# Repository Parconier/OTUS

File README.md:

# OTUS: 3D Printed Robotics Kit by Parconier 

[Click here to purchase one from the Abierto shop](https://www.abierto.cc/shop/#tags=10849|10852 "abierto.cc")

# Files in this repository

.STL - This files are for 3D printing, if you want to edit any of them, feel free to use the .STEP file.
.STEP - This files contains every pattern in a generic 3D format that you can easily edit.

# Name format

name of the piece "\_" suggestion of color of neutral "\_" ammount per kit "\- v" version of the file

Example:
Patternx2\_color\_x6 \-  v1.0

# License

Copyright CERN 2013. 

This documentation describes Open Hardware and is licensed under the CERN OHL v. 1.2. This means that you are free to use, reproduce, sell or modify our designs in any way you see fit, as long as you retain this same license for your projects using our work. For those wanting to use our hardware designs and/or software packages, we require you:

Label the product as a clone. It must be clear that it is not a product from our factory.
Note that "OTUS is a registered trademark of Parconier".
Host your own copy of the source files on your own server or similar, even if they are unmodified. Do not just point to our existing source.

You may redistribute and modify this documentation under the terms of the CERN OHL v.1.2. (http://ohwr.org/cernohl). This documentation is distributed WITHOUT ANY EXPRESS OR IMPLIED WARRANTY, INCLUDING OF MERCHANTABILITY, SATISFACTORY QUALITY AND FITNESS FOR A PARTICULAR PURPOSE. Please see the CERN OHL v.1.2 for applicable conditions.

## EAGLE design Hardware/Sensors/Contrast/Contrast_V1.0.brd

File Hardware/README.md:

# PCB files for the OTUS 3D Printed Robotics Kit  

[Click here to purchase OTUS PCB boards from the Abierto shop](https://www.abierto.cc/shop/product/67049/otus-electronica/ "abierto.cc")

 Format is EagleCAD for Schematic and board layout.

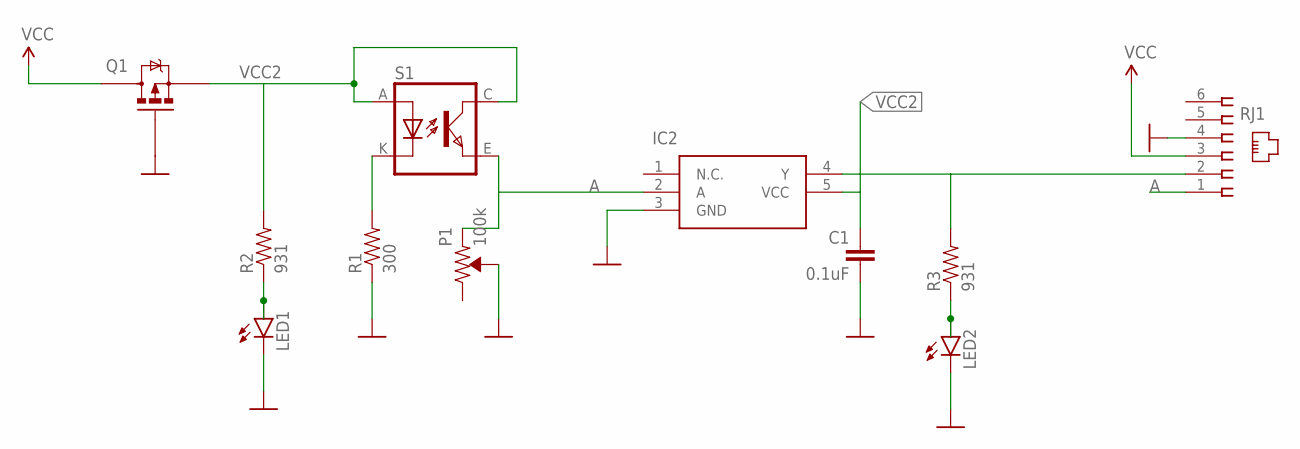
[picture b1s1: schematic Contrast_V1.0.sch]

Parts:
C1: 0.1uF; 0402; MPN CC0402KRX5R9BB104
IC2: 74LVC1G14GW-Q100,1; SOT65P212X110-5N; MPN 74AHC1G14GW-Q100,1
LED1: LED0603; LED-0603; MPN LTST-C193KRKT-5A
LED2: LED0603; LED-0603; MPN LB Q39E-L2OO-35-1
P1: 100k; 3309W-1-104; MPN 3309W-1-104
Q1: RU1C002ZPTCL; SOTFL65P210X105-3N; MPN RU1C002ZPTCL
R1: 300; RESC1005X35; MPN RC0402JR-07300RL
R2, R3: 931; RESC1005X35; MPN RC0402FR-07931RL
RJ1: 615006138421; MPN 54601-906WPLF
S1: TCRT5000; MPN TCRT5000

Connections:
A: IC2.2 (A), P1.1 (CCW), RJ1.1, S1.E (EMITTER)
GND: C1.2, IC2.3 (GND), LED1.C, LED2.C, P1.2 (WIPER), Q1.1 (G), R1.1, RJ1.4
unnamed: R1.2, S1.K (CATHODE)
unnamed: IC2.4 (Y), R3.2, RJ1.2
unnamed: LED2.A, R3.1
unnamed: LED1.A, R2.1
VCC: Q1.3 (D), RJ1.3
VCC2: C1.1, IC2.5 (VCC), Q1.2 (S), R2.2, S1.A (ANODE), S1.C (COLLECTOR)

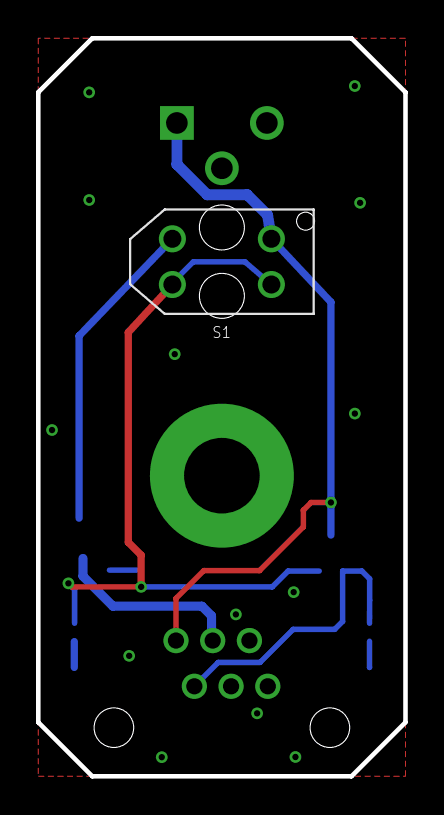
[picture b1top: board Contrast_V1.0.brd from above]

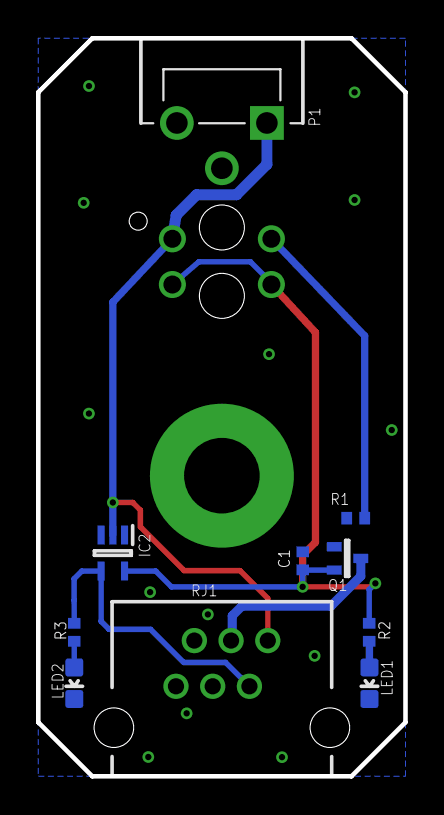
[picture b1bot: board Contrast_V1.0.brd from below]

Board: 2 copper layers, 20.4 x 41.0 mm, 11 parts (10 on the bottom side), 8 nets.

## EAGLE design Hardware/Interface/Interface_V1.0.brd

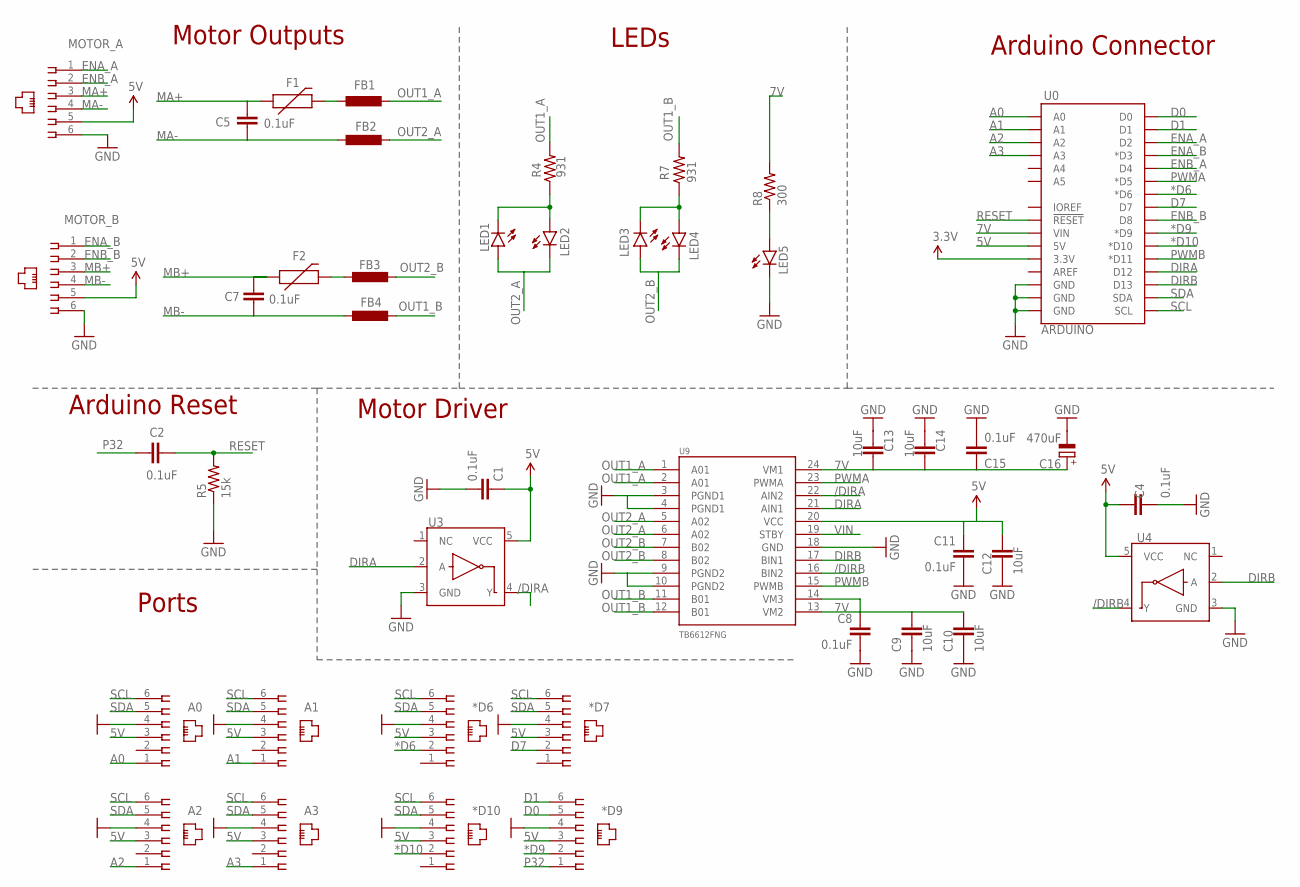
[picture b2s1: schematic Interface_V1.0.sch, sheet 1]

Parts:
*D6, *D7, *D9, *D10: 615006138421; MPNCH 623-PCB-6P6C
A0, A1, A2, A3: 615006138421; MPNCH 623-PCB-6P6C
C1, C2, C4, C5, C7, C8, C11, C15: 0.1uF; 0402; MPN CC0402KRX5R9BB104
C9, C10, C12, C13, C14: 10uF; C0603; MPN ZRB18AR61E106ME01L
C16: 470uF; PANASONIC_E; MPN EDH477M016A9MAA
F1, F2: PTC; PTC-1206; MPN 0ZCJ0100FF2E
FB1, FB2, FB3, FB4: FERRITE_BEAD; F0805; MPN 2508056017Y2
LED1, LED2, LED3, LED4: LED0603; LED-0603; MPN LTST-C193KRKT-5A
LED5: LED0603; LED-0603; MPN LW Q38G-Q2OO-3K5L-1
MOTOR_A: 615006138421; MPNCH 9901-6P6C
MOTOR_B: 615006138421; MPNCH 9901-6P6C
R4, R7: 931; RESC1005X35; MPN RC0402FR-07931RL
R5: 15k; RESC1005X35; MPN RC0402FR-0715KL
R8: 300; RESC1005X35; MPN RC0402JR-07300RL
U0: ARDUINO; ARDUINO_R3_NO_HOLES_SPI
U3, U4: INVERTER""; SC70; MPN 74AHC1G14GW-Q100,1
U9: TB6612FNG; SSOP24; MPN TB6612FNG,C,8,EL

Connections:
3.3V: U0.3.3V
5V: *D6.3, *D7.3, *D9.3, *D10.3, A0.3, A1.3, A2.3, A3.3, C1.1, C4.1, C11.1, C12.1, MOTOR_A.5, MOTOR_B.5, U0.5V, U3.5 (VCC), U4.5 (VCC), U9.20 (VCC)
7V: C8.1, C9.1, C10.1, C13.1, C14.1, C15.1, C16.+, R8.2, U0.VIN, U9.13 (VM2), U9.14 (VM3), U9.24 (VM1); also elsewhere on the board
*D6: *D6.2, U0.D6 (*D6)
*D9: *D9.2, U0.D9 (*D9)
*D10: *D10.2, U0.D10 (*D10)
/DIRA: U3.4 (Y), U9.22 (AIN2)
/DIRB: U4.4 (Y), U9.16 (BIN2)
A0: A0.1, U0.A0
A1: A1.1, U0.A1
A2: A2.1, U0.A2
A3: A3.1, U0.A3
D0: *D9.5, U0.D0
D1: *D9.6, U0.D1
D7: *D7.2, U0.D7
DIRA: U0.D12, U3.2 (A), U9.21 (AIN1)
DIRB: U0.D13, U4.2 (A), U9.17 (BIN1)
ENA_A: MOTOR_A.1, U0.D2
ENA_B: MOTOR_B.1, U0.D3 (*D3)
ENB_A: MOTOR_A.2, U0.D4
ENB_B: MOTOR_B.2, U0.D8
GND: *D6.4, *D7.4, *D9.4, *D10.4, A0.4, A1.4, A2.4, A3.4, C1.2, C4.2, C8.2, C9.2, C10.2, C11.2, C12.2, C13.2, C14.2, C15.2, C16.-, LED5.C, MOTOR_A.6, MOTOR_B.6, R5.1, U0.GND@1 (GND), U0.GND@2 (GND), U0.GND@3 (GND), U3.3 (GND), U4.3 (GND), U9.3 (PGND1), U9.4 (PGND1), U9.9 (PGND2), U9.10 (PGND2), U9.18 (GND); also elsewhere on the board
MA+: C5.1, F1.1, MOTOR_A.3
MA-: C5.2, FB2.1, MOTOR_A.4
MB+: C7.1, F2.1, MOTOR_B.3
MB-: C7.2, FB4.1, MOTOR_B.4
unnamed: LED1.C, LED2.A, R4.1
unnamed: LED3.C, LED4.A, R7.1
unnamed: F1.2, FB1.1
unnamed: F2.2, FB3.1
unnamed: LED5.A, R8.1
OUT1_A: FB1.2, R4.2, U9.1 (A01), U9.2 (A01)
OUT1_B: FB4.2, R7.2, U9.11 (B01), U9.12 (B01)
OUT2_A: FB2.2, LED1.A, LED2.C, U9.5 (A02), U9.6 (A02)
OUT2_B: FB3.2, LED3.A, LED4.C, U9.7 (B02), U9.8 (B02)
P32: *D9.1, C2.1
PWMA: U0.D5 (*D5), U9.23 (PWMA)
PWMB: U0.D11 (*D11), U9.15 (PWMB)
RESET: C2.2, R5.2, U0.RESET@1 (!RESET!)
SCL: *D6.6, *D7.6, *D10.6, A0.6, A1.6, A2.6, A3.6, U0.SCL
SDA: *D6.5, *D7.5, *D10.5, A0.5, A1.5, A2.5, A3.5, U0.SDA
VIN: U9.19 (STBY); also elsewhere on the board

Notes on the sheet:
Motor Outputs
LEDs
Arduino Connector
Motor Driver
Arduino Reset
Ports

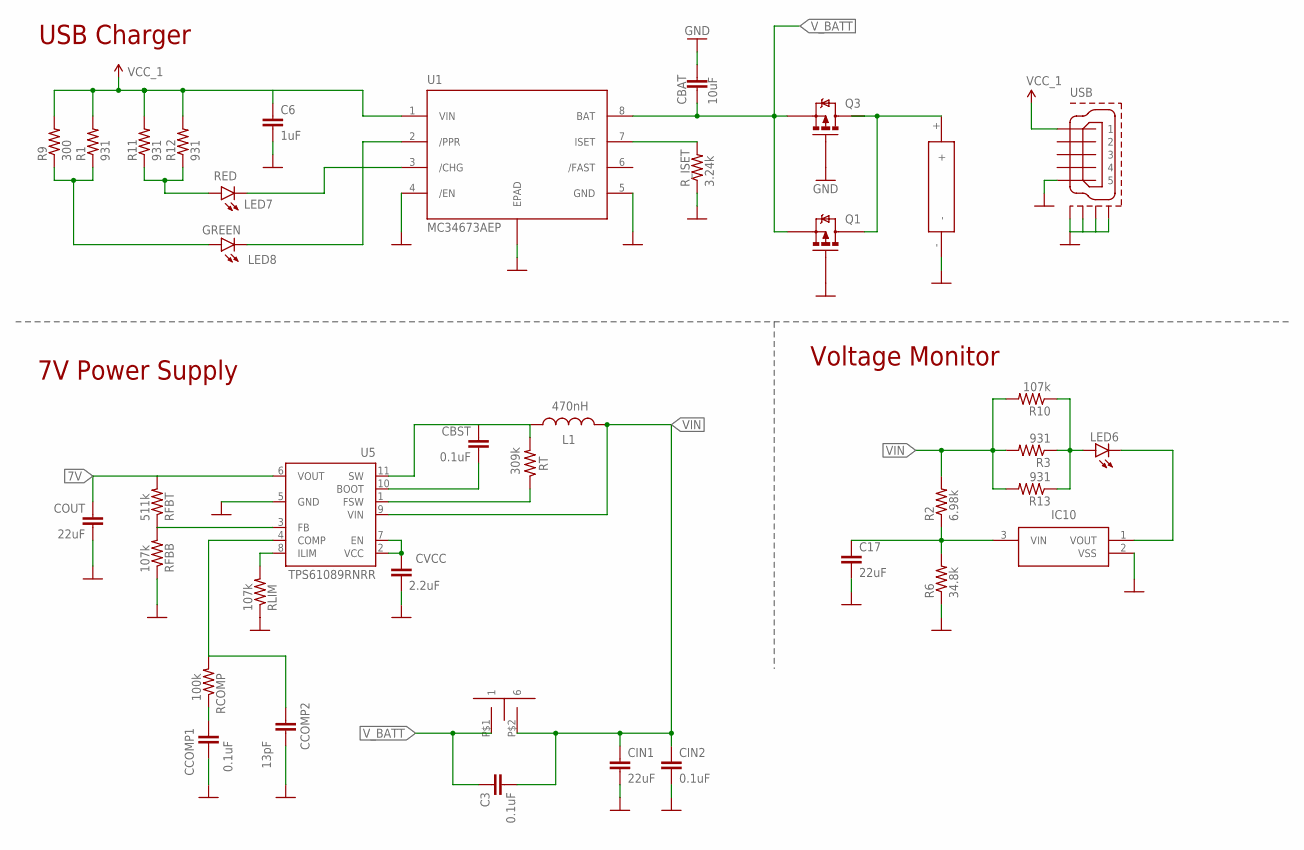
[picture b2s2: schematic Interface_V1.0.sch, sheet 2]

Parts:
B1: GPTS203212B; GPTS_RIGHT_ANGLE; MPN GPTS203212B
BATT: BATTERY; THM_HOLDER; MPN 1043
C3: 0.1uF; 0402; MPN CC0402KRX5R9BB104
C6: 1uF; 0402; MPN CC0402ZRY5V6BB105
C17: 22uF; C0603; MPN GRM188R61A226ME15D
CBAT: 10uF; C0603; MPN ZRB18AR61E106ME01L
CBST: 0.1uF; 0402; MPN CC0402KRX5R9BB104
CCOMP1: 0.1uF; 0402; MPN CC0402KRX5R9BB104
CCOMP2: 13pF; 0402; MPN CL05C130JB5NCNC
CIN1: 22uF; C0603; MPN GRM188R61A226ME15D
CIN2: 0.1uF; 0402; MPN CC0402KRX5R9BB104
COUT: 22uF; C1210; MPN GRM32ER61E226KE15L
CVCC: 2.2uF; C0603; MPN GRM188R61E225MA12D
IC10: TC54VN3002ECB713; SOT95P275X130-3N; MPN TC54VN3002ECB713
L1: 470nH; L2520; MPN DFE252012P-R47M=P2
LED6, LED7: LED0603; LED-0603; MPN LTST-C193KRKT-5A
LED8: LED0603; LED-0603; MPN LT Q39E-Q1OO-25-1
Q1: IRLML2244TRPBF; SOT95P237X112-3N; MANUFACTURER_PART_NUMBER IRLML2244TRPBF
Q3: IRLML2244TRPBF; SOT95P237X112-3N; MPN IRLML2244TRPBF
R1, R3, R11, R12, R13: 931; RESC1005X35; MPN RC0402FR-07931RL
R2: 6.98k; RESC1005X35; MPN RC0402FR-076K98L
R6: 34.8k; RESC1005X35; MPN RC0402FR-0734K8L
R9: 300; RESC1005X35; MPN RC0402JR-07300RL
R10: 107k; RESC1005X35; MPN RC0402FR-07107KL
RCOMP: 100k; RESC1005X35; MPN RC0402FR-07100KL
RFBB: 107k; RESC1005X35; MPN RC0402FR-07107KL
RFBT: 511k; RESC1005X35; MPN RC0402FR-07511KL
RLIM: 107k; RESC1005X35; MPN RC0402FR-07107KL
RT: 309k; RESC1005X35; MPN AC0402FR-07309KL
R_ISET: 3.24k; RESC1005X35; MPN RC0402FR-073K24L
U1: MC34673AEP; SOT1590-2; MPN MC34673AEPR2
U5: TPS61089RNRR; VQFN-11; MPN TPS61089RNRR
USB: MOLEX-47346-0001MOKO; A01SBXXXXXXX-470-MOKO; MPN 0473460001

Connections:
7V: COUT.1, RFBT.2, U5.6 (VOUT); also elsewhere on the board
GND: BATT.-, C6.2, C17.2, CBAT.1, CCOMP1.2, CCOMP2.2, CIN1.2, CIN2.2, COUT.2, CVCC.2, IC10.2 (VSS), Q1.1 (G), Q3.1 (G), R6.1, RFBB.1, RLIM.1, R_ISET.1, U1.4 (/EN), U1.5 (GND), U1.9 (EPAD), U5.5 (GND), USB.5, USB.GND1, USB.GND2, USB.GND3, USB.GND4, USB.GND5 (GND3), USB.GND6 (GND3); also elsewhere on the board
GREEN: LED8.C, U1.2 (/PPR)
unnamed: LED7.A, R11.1, R12.1
unnamed: LED8.A, R1.1, R9.1
unnamed: IC10.1 (VOUT), LED6.C
unnamed: C17.1, IC10.3 (VIN), R2.1, R6.2
unnamed: LED6.A, R3.1, R10.1, R13.1
unnamed: R_ISET.2, U1.7 (ISET)
unnamed: CVCC.1, U5.2 (VCC), U5.7 (EN)
unnamed: CBST.1, L1.2, RT.2, U5.11 (SW)
unnamed: RT.1, U5.1 (FSW)
unnamed: CBST.2, U5.10 (BOOT)
unnamed: RFBB.2, RFBT.1, U5.3 (FB)
unnamed: CCOMP2.1, RCOMP.2, U5.4 (COMP)
unnamed: CCOMP1.1, RCOMP.1
unnamed: RLIM.2, U5.8 (ILIM)
RED: LED7.C, U1.3 (/CHG)
VCC_1: C6.1, R1.2, R9.2, R11.2, R12.2, U1.1 (VIN), USB.1
VIN: B1.P$2 (6), C3.2, CIN1.1, CIN2.1, L1.1, R2.2, R3.2, R10.2, R13.2, U5.9 (VIN); also elsewhere on the board
V_B: BATT.+, Q1.3 (D), Q3.3 (D)
V_BATT: B1.P$1 (1), C3.1, CBAT.2, Q1.2 (S), Q3.2 (S), U1.8 (BAT)

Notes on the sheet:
RED
GREEN
USB Charger
7V Power Supply
Voltage Monitor

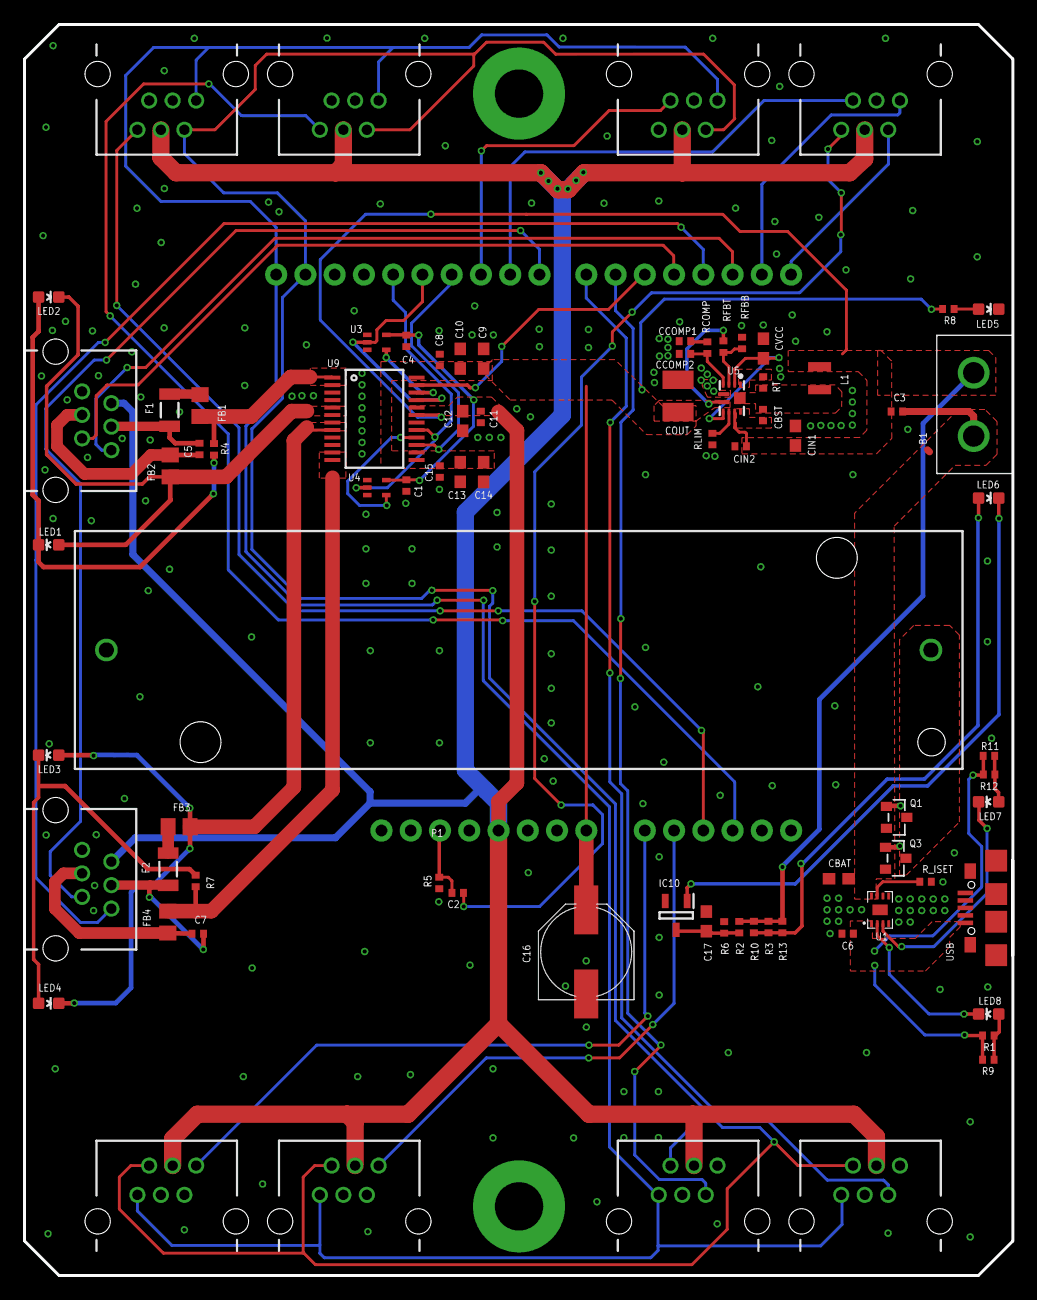
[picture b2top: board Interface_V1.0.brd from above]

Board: 2 copper layers, 85.8 x 108.6 mm, 81 parts (0 on the bottom side), 60 nets.

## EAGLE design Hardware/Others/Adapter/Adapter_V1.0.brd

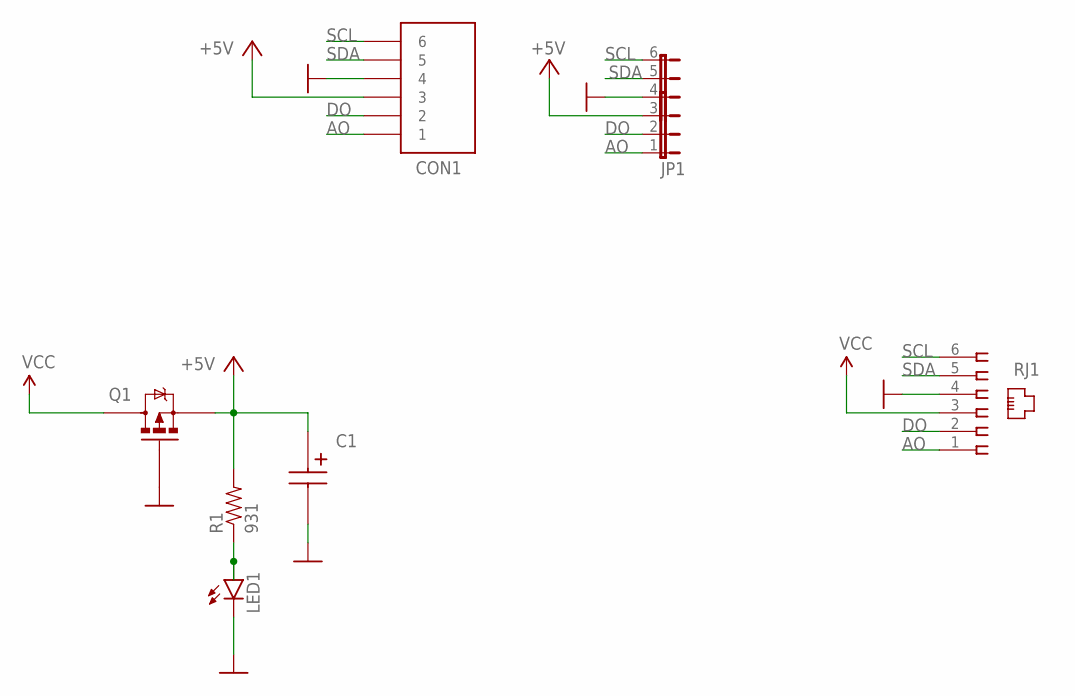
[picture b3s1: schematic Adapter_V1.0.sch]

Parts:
C1: 220uF; CAPPRD200W80D500H1100; MPN 227CKS010M
CON1: 1990041KF250A-2.5-6P; KF250A-2.5-6P; MPN 1990041
JP1: JP6E; JP6
LED1: LED0603; LED-0603; MPN LTST-C193KRKT-5A
Q1: IRLML2244TRPBF; SOT95P237X112-3N; MANUFACTURER_PART_NUMBER IRLML2244TRPBF
R1: 931; RESC1005X35; MPN RC0402FR-07931RL
RJ1: 615006138421; MPN 615006138421

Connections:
+5V: C1.1 (+), CON1.3, JP1.3, Q1.2 (S), R1.2
AO: CON1.1, JP1.1, RJ1.1
DO: CON1.2, JP1.2, RJ1.2
GND: C1.2 (-), CON1.4, JP1.4, LED1.C, Q1.1 (G), RJ1.4
unnamed: LED1.A, R1.1
SCL: CON1.6, JP1.6, RJ1.6
SDA: CON1.5, JP1.5, RJ1.5
VCC: Q1.3 (D), RJ1.3

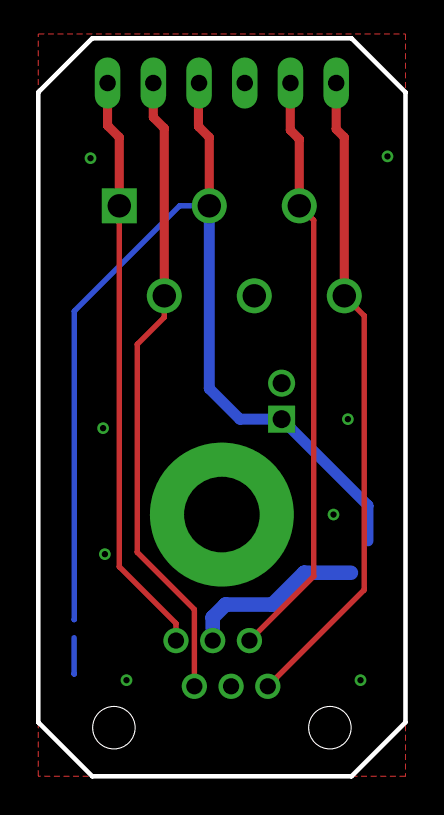
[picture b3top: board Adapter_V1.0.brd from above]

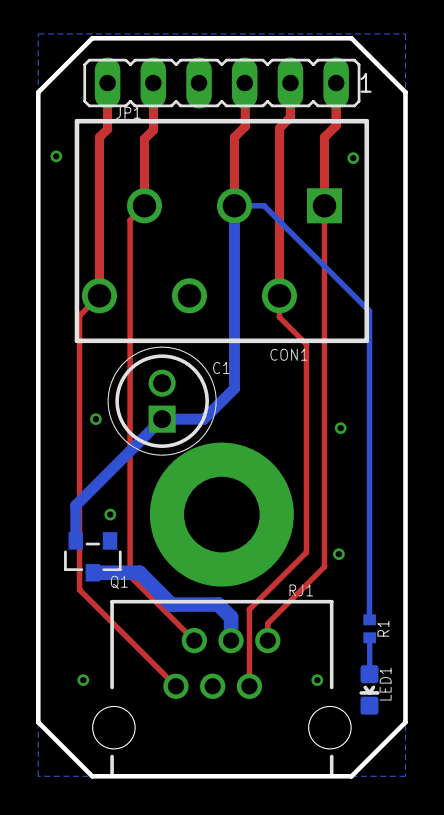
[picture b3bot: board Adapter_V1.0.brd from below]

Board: 2 copper layers, 20.4 x 41.0 mm, 7 parts (7 on the bottom side), 8 nets.

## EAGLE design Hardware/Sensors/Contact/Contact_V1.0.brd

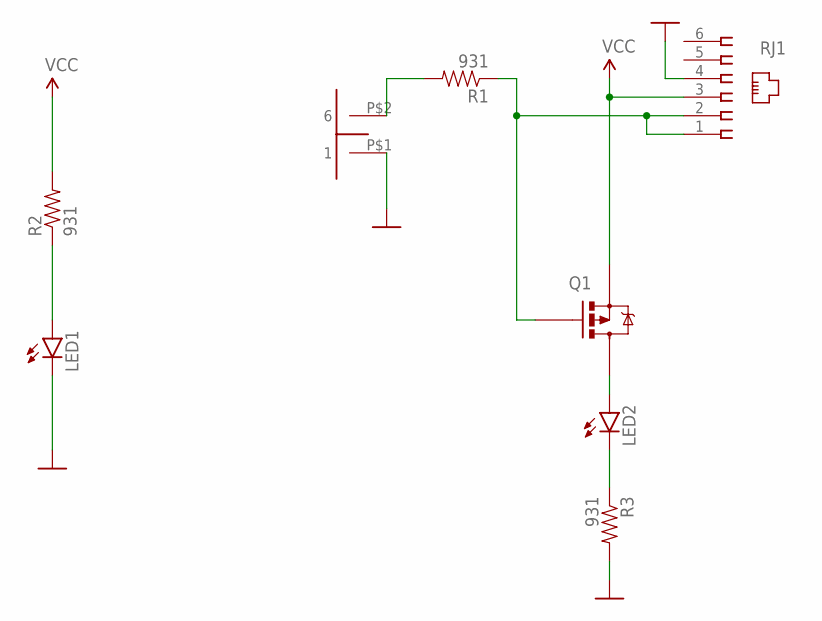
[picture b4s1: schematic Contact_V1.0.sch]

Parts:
LED1: LED0603; LED-0603; MPN LTST-C193KRKT-5A
LED2: LED0603; LED-0603; MPN LB Q39E-L2OO-35-1
PB1: PUSHBUTTON_MOKO; SUBSTITUTE_FSM104_RIGHT_ANGLE
Q1: RU1C002ZPTCL; SOTFL65P210X105-3N; MPN RU1C002ZPTCL
R1, R2, R3: 931; RESC1005X35; MPN RC0402FR-07931RL
RJ1: 615006138421; MPN 615006138421

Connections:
GND: LED1.C, PB1.P$1 (1), R3.2, RJ1.4
unnamed: PB1.P$2 (6), R1.2
unnamed: Q1.1 (G), R1.1, RJ1.1, RJ1.2
unnamed: LED2.A, Q1.3 (D)
unnamed: LED2.C, R3.1
unnamed: LED1.A, R2.1
VCC: Q1.2 (S), R2.2, RJ1.3

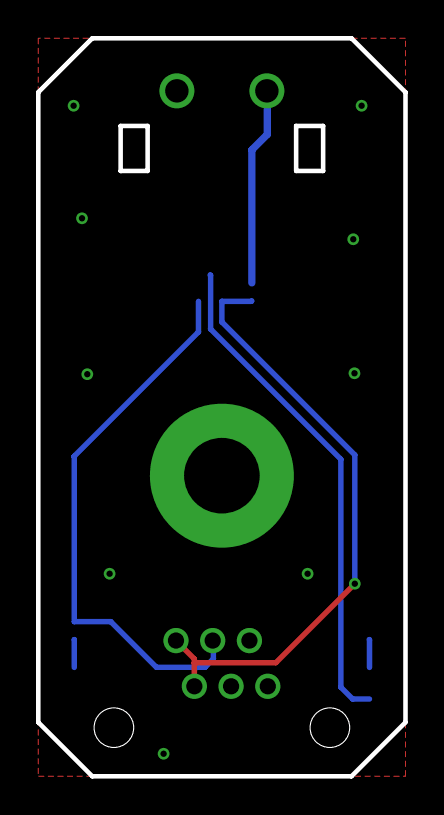
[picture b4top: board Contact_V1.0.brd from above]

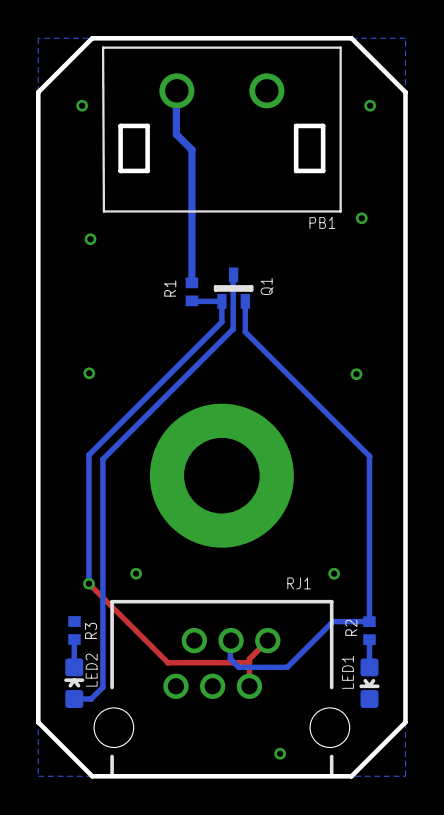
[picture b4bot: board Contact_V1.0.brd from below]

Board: 2 copper layers, 20.4 x 41.0 mm, 8 parts (8 on the bottom side), 7 nets.

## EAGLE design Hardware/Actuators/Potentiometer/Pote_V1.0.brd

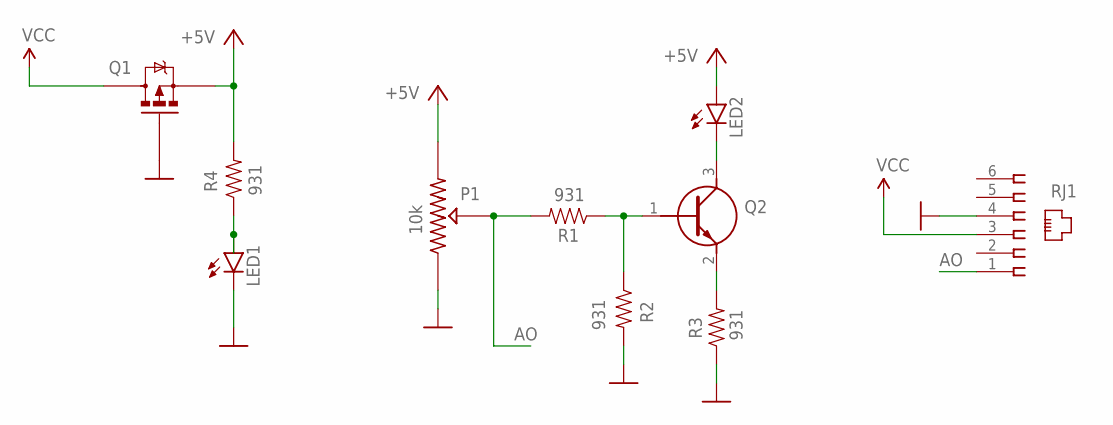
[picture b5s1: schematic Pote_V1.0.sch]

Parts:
LED1: LED0603; LED-0603; MPN LTST-C193KRKT-5A
LED2: LED0603; LED-0603; MPN LB Q39E-L2OO-35-1
P1: 10k; PTV09A-2015F; MPN PTV09A-2025F-B103
Q1: RU1C002ZPTCL; SOTFL65P210X105-3N; MPN RU1C002ZPTCL
Q2: MMBT3904,215; SOT95P230X110-3N; MPN MMBT3904,215
R1, R2, R3, R4: 931; RESC1005X35; MPN RC0402FR-07931RL
RJ1: 615006138421; MPN 615006138421

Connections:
+5V: LED2.A, P1.3 (R_2), Q1.2 (S), R4.2
AO: P1.2 (WIPER), R1.2, RJ1.1
GND: LED1.C, P1.1 (R_1), Q1.1 (G), R2.2, R3.1, RJ1.4
unnamed: Q2.2 (E), R3.2
unnamed: LED2.C, Q2.3 (C)
unnamed: Q2.1 (B), R1.1, R2.1
unnamed: LED1.A, R4.1
VCC: Q1.3 (D), RJ1.3

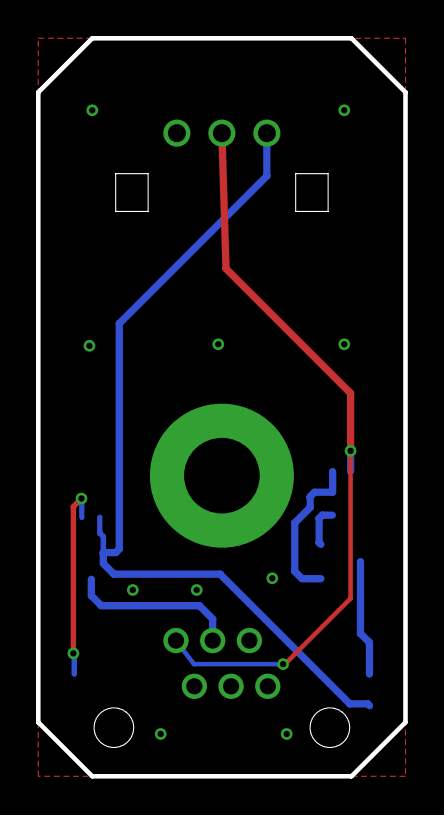
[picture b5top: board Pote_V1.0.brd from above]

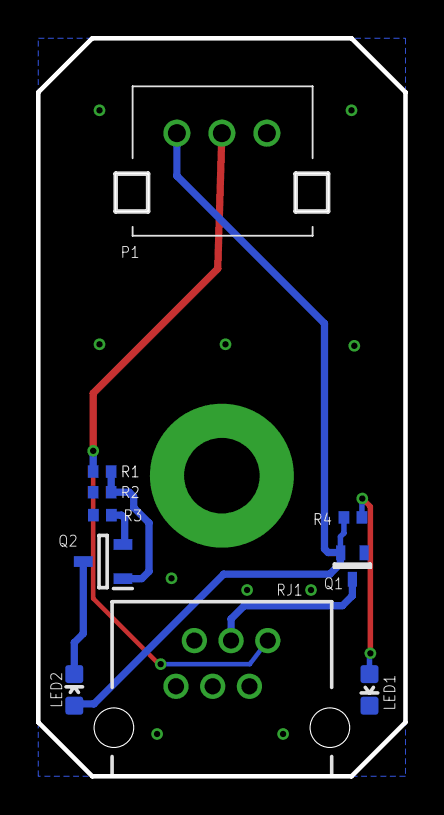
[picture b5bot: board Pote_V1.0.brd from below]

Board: 2 copper layers, 20.4 x 41.0 mm, 10 parts (10 on the bottom side), 8 nets.

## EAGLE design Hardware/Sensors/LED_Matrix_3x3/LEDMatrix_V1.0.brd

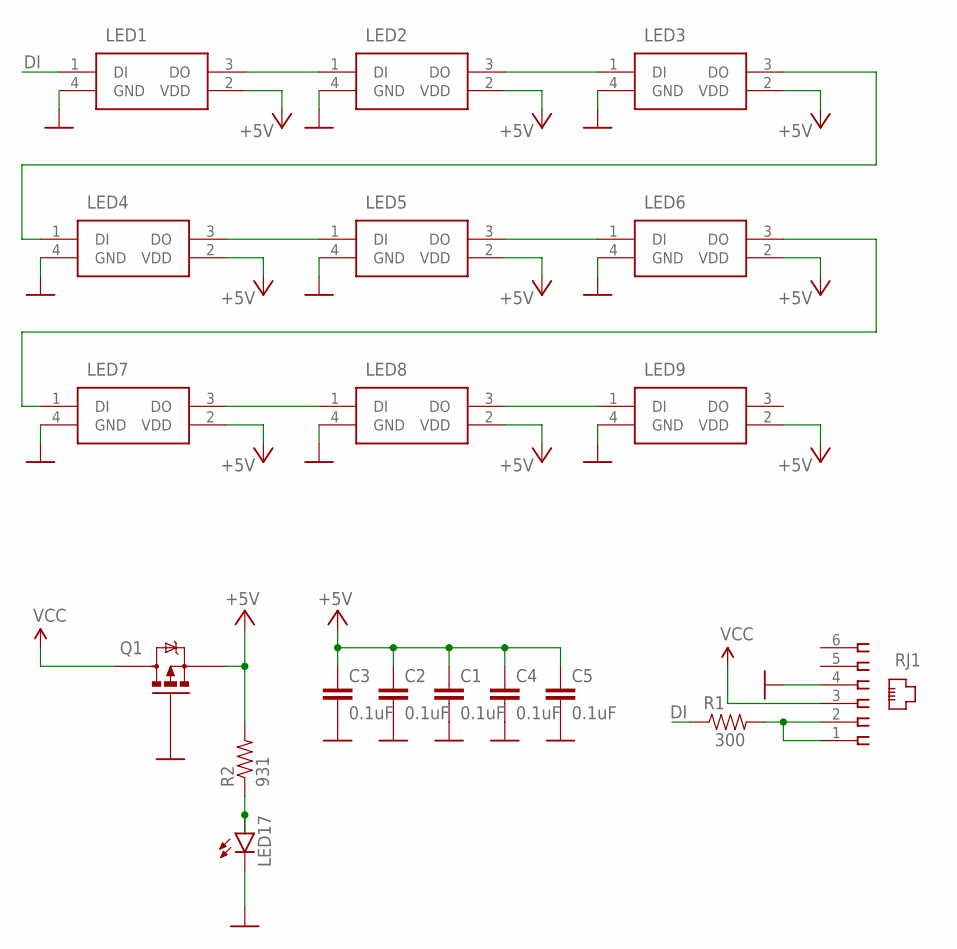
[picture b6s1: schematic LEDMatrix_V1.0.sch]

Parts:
C1, C2, C3, C4, C5: 0.1uF; 0402; MPN CC0402KRX5R9BB104
LED1, LED2, LED3, LED4, LED5, LED6, LED7, LED8, LED9: SK6812MINI; MPN SK6812MINI
LED17: LED0603; LED-0603; MPN LTST-C193KRKT-5A
Q1: IRLML2244TRPBF; SOT95P237X112-3N; MANUFACTURER_PART_NUMBER IRLML2244TRPBF
R1: 300; RESC1005X35; MPN RC0402JR-07300RL
R2: 931; RESC1005X35; MPN RC0402FR-07931RL
RJ1: 615006138421; MPN 615006138421

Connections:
+5V: C1.1, C2.1, C3.1, C4.1, C5.1, LED1.2 (VDD), LED2.2 (VDD), LED3.2 (VDD), LED4.2 (VDD), LED5.2 (VDD), LED6.2 (VDD), LED7.2 (VDD), LED8.2 (VDD), LED9.2 (VDD), Q1.2 (S), R2.2
DI: LED1.1 (DI), R1.1
GND: C1.2, C2.2, C3.2, C4.2, C5.2, LED1.4 (GND), LED2.4 (GND), LED3.4 (GND), LED4.4 (GND), LED5.4 (GND), LED6.4 (GND), LED7.4 (GND), LED8.4 (GND), LED9.4 (GND), LED17.C, Q1.1 (G), RJ1.4
unnamed: LED1.3 (DO), LED2.1 (DI)
unnamed: LED2.3 (DO), LED3.1 (DI)
unnamed: LED3.3 (DO), LED4.1 (DI)
unnamed: LED5.3 (DO), LED6.1 (DI)
unnamed: LED17.A, R2.1
unnamed: LED4.3 (DO), LED5.1 (DI)
unnamed: LED6.3 (DO), LED7.1 (DI)
unnamed: LED7.3 (DO), LED8.1 (DI)
unnamed: LED8.3 (DO), LED9.1 (DI)
unnamed: R1.2, RJ1.1, RJ1.2
VCC: Q1.3 (D), RJ1.3

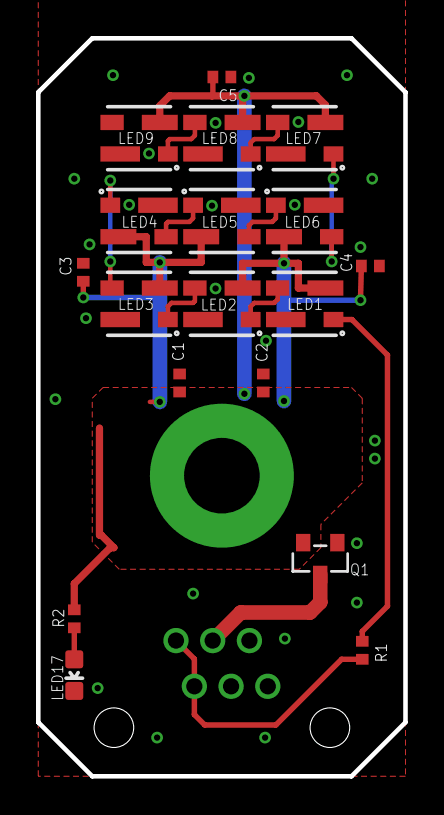
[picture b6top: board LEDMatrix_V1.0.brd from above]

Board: 2 copper layers, 20.4 x 41.0 mm, 19 parts (1 on the bottom side), 14 nets.

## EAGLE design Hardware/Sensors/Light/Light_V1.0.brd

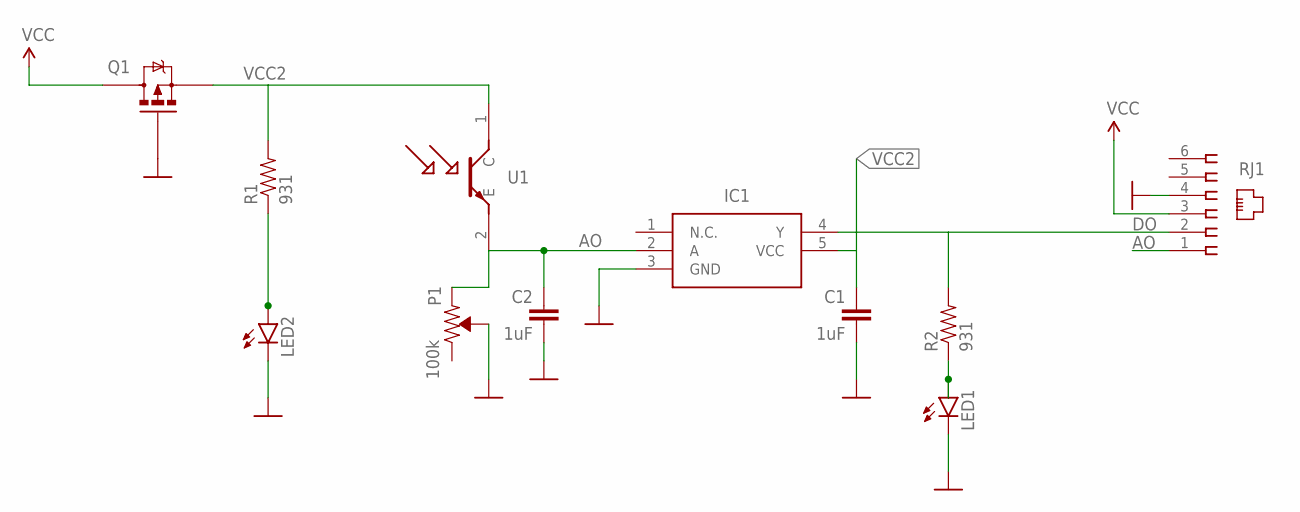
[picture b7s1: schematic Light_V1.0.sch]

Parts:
C1, C2: 1uF; 0402; MPN CC0402ZRY5V6BB105
IC1: 74LVC1G14GW-Q100,1; SOT65P212X110-5N; MPN 74AHC1G14GW-Q100,1
LED1: LED0603; LED-0603; MPN LB Q39E-L2OO-35-1
LED2: LED0603; LED-0603; MPN LTST-C193KRKT-5A
P1: 100k; 3309W-1-104; MPN 3309W-1-104
Q1: RU1C002ZPTCL; SOTFL65P210X105-3N; MPN RU1C002ZPTCL
R1, R2: 931; RESC1005X35; MPN RC0402FR-07931RL
RJ1: 615006138421; MPN 54601-906WPLF
U1: NJL7302L-F3; MPN NJL7302L-F3

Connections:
AO: C2.1, IC1.2 (A), P1.1 (CCW), RJ1.1, U1.2 (E)
DO: IC1.4 (Y), R2.2, RJ1.2
GND: C1.2, C2.2, IC1.3 (GND), LED1.C, LED2.C, P1.2 (WIPER), Q1.1 (G), RJ1.4
unnamed: LED1.A, R2.1
unnamed: LED2.A, R1.1
VCC: Q1.3 (D), RJ1.3
VCC2: C1.1, IC1.5 (VCC), Q1.2 (S), R1.2, U1.1 (C)

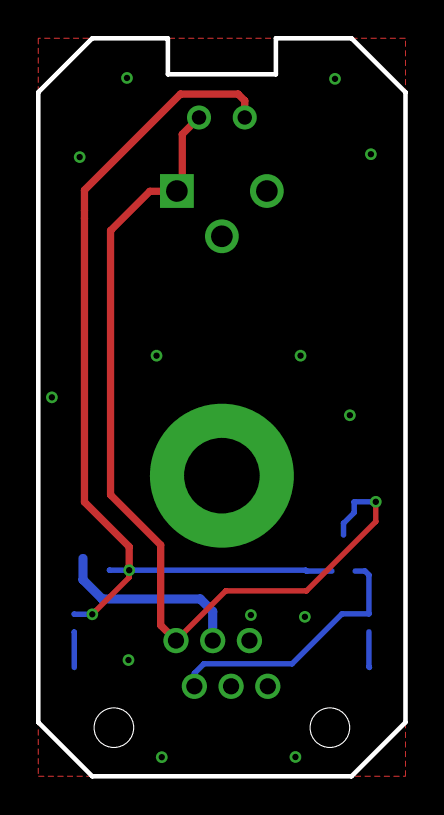
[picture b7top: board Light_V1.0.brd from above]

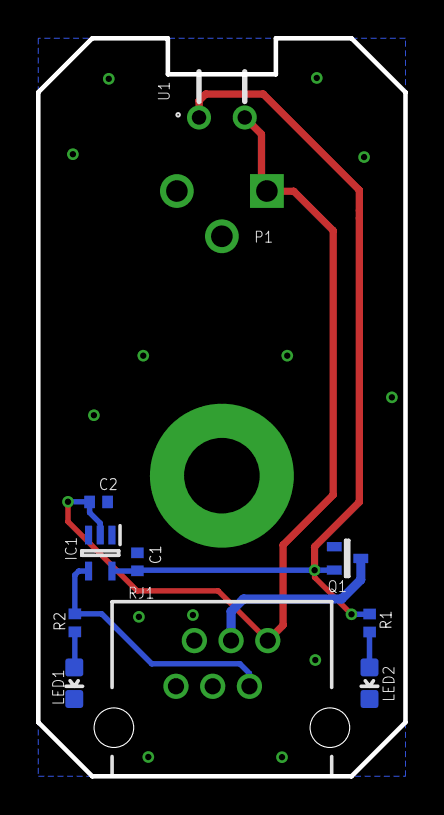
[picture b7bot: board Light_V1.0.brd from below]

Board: 2 copper layers, 20.4 x 41.0 mm, 11 parts (11 on the bottom side), 7 nets.

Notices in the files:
parts and their libraries:
SparkFun-LED: Licensing: Creative Commons ShareAlike 4.0 International - https://creativecommons.org/licenses/by-sa/4.0
MyFrames: Released under the Creative Commons
MyFrames: https://creativecommons.org/licenses/by-sa/4.0
